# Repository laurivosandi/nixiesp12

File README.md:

# NixiESP12

## Intro

Yet another Nixie clock project!

Some highlights:

* K155ID1 driven IN-12A or IN-12B tubes for hour, minute, seconds. Use 36k resistors on these tubes.
* BS108 driven IN-6 or [similar 4*10mm neon bulbs](https://www.aliexpress.com/item/32344955038.html?spm=a2g0s.9042311.0.0.6ab14c4dCxpPZ0) for digit separation. Use 270k resistors on these bulbs.
* 74HC595 for serial to parallel conversion
* ESP8266 for time synchronization. Use 1k resistors for pull-up.
* LM1117-3.3V and LM1117-5V regulators for logic power supply
* No tube step up converter on-board, pin headers for connecting
  <a href="http://www.ebay.com/itm/DC-5V-12V-to-170V-DC-High-Voltage-NIXIE-Power-Supply-Module-PSU-NIXIE-TUBE-ERA-/322511957768?hash=item4b1735ef08">third party power supply</a>
* KiCad design with 3D models from http://miniwatt.info

Some KiCad screenshots:

## Install

Install dependencies on an Ubuntu 18.04 box:

```bash
apt install -y python3-pip wget picocom make
pip3 install adafruit-ampy esptool
```

Boot ESP8266 with program pin held low and flash MicroPython:

```bash
cd firmware
make erase
make flash
```

Reboot ESP8266, open serial to to the controller and format filesystem:

```
import os
os.umount('/')
os.VfsLfs2.mkfs(bdev)
os.mount(bdev, '/')
```

Finish with by uploading scripts:

```bash
make upload
```

Power cycle the device and via WiFi connect to the device,
network name is MicroPython-XXXXXX and password is micropythoN.
Navigate to http://192.168.4.1 to start the configuration wizard.

## Configuring

If firmware is unable to connect to preconfigured wireless network
or it is started up for the first time wireless network
with password `micropythoN` is created.

Connect to that wireless network and open http://192.168.4.1
in web browser to configure the clock.

## Assembly tips

Some cheap 1117V regulators don't offer short circuit protection
and once blown pass through input voltage,
make sure you get ones with protection otherwise you can fry ESP8266
or serial-to-parallel chips.

Once the PCB is milled or etched make sure you clean the 180V rails thoroughly,
that voltage is high enough to cross gaps of 0.1mm.
Once that happens it burns a thick dark trace into the fiberglass of PCB and
it's pretty tricky to clean up.
The PCB is designed with 0.4mm clearance to be compliant with HV designs.
This clearance of course assumes that PCB traces are covered.
Either use solder mask or conformal coating.

Use the bench power supply to gradually power up the device,
at 9V set current limiter to 0.5A max.
5V linear regulator can be omitted and bypassed if 5V wall adapter is always used.
Otherwise 6V-12V wall adapters are suitable,
Thincan DBE60 9V wall adapters are pretty much perfect for the job.
Note that the higher the input voltage the more power is dissipated
as heat on the 3.3V and 5V voltage regulators, thus at 12V the device gets really hot.

## Debugging

* If you get nonsense reading during boot up sequence 0..9 likely the connection between serial-to-parallel chips and high voltage drivers
  is flaky. Either there are shorted pins or there is no connection at all. Check soldering joints and check for shorts between lines and line to ground.
* If single tube doesn't light up likely the gas has escaped the tube, find replacement tube.
* If single digit does not light up likely the tube socket pin is mangled or it is not properly soldered on the side where the PCB trace runs.

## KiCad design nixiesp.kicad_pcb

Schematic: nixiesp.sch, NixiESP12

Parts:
C1, C3: C; C_Disc_D4.3mm_W1.9mm_P5.00mm
C2, C4: CP; CP_Radial_D8.0mm_P3.50mm
J1: Power 9-15V; TerminalBlock_Pheonix_PT-3.5mm_2pol
J2: ESP8266; Socket_Strip_Straight_2x04_Pitch2.54mm
J3, J10, J12: CONN_01X06; Pin_Header_Angled_1x06_Pitch2.54mm
J4, J6, J13: CONN_01X07; Pin_Header_Angled_1x07_Pitch2.54mm
J5, J27, J29: CONN_01X06; Socket_Strip_Straight_1x06_Pitch2.54mm
J9: CONN_01X05; Socket_Strip_Straight_1x05_Pitch2.54mm
J11, J14, J31: CONN_01X07; Socket_Strip_Straight_1x07_Pitch2.54mm
J15, J16, J17, J18, J19, J20, J21, J23, J24, J25: CONN_01X01; 1pin
N1: HX:MM:SS; russian-nixies-IN-12
N2: XH:MM:SS; russian-nixies-IN-12
N3: HH:MX:SS; russian-nixies-IN-12
N4: HH:XM:SS; russian-nixies-IN-12
N5: HH:MM:SX; russian-nixies-IN-12
N6: HH:MM:XS; russian-nixies-IN-12
N7, N8, N9, N10: IN-6; russian-nixies-IN-6
Q1, Q2, Q3, Q4: BS107; TO-92_Inline_Wide
R1, R2: 2.2k; R_Axial_DIN0207_L6.3mm_D2.5mm_P7.62mm_Horizontal
R7, R8, R9, R10: 15k; R_Axial_DIN0207_L6.3mm_D2.5mm_P7.62mm_Horizontal
R11, R12, R13, R14, R15, R16: 10k; R_Axial_DIN0207_L6.3mm_D2.5mm_P7.62mm_Horizontal
U1, U5, U8, U11, U13, U14: 74HC595; DIP-16_W7.62mm
U2, U3, U4, U6, U7, U9: K155ID1; DIP-16_W7.62mm
U10: LM1117-5.0; SOT-223
U12: LM1117-3.3; SOT-223

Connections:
/data: J2.3, R2.2, U8.14 (SER)
/latch: J2.5, R1.1, U1.12 (RCLK), U5.12 (RCLK), U8.12 (RCLK), U11.12 (RCLK), U13.12 (RCLK), U14.12 (RCLK)
unnamed: J1.2, J9.1, U10.3 (VI), U12.3 (VI)
unnamed: J3.2, U2.7
unnamed: J3.3, U2.6
unnamed: J3.5, U2.4
unnamed: J3.6, U2.3
unnamed: J4.2, U3.7
unnamed: J4.3, U3.6
unnamed: J4.5, U3.4
unnamed: J4.6, U3.3
unnamed: J4.7, Q1.2 (G)
unnamed: J5.1, U1.2 (QC)
unnamed: J5.2, U1.3 (QD)
unnamed: J5.3, U1.4 (QE)
unnamed: J5.5, U1.5 (QF)
unnamed: J5.6, U1.6 (QG)
unnamed: J6.2, U6.7
unnamed: J6.3, U6.6
unnamed: J6.5, U6.4
unnamed: J6.6, U6.3
unnamed: J6.7, Q3.2 (G)
unnamed: J10.1, Q2.2 (G)
unnamed: J10.2, U4.7
unnamed: J10.3, U4.6
unnamed: J10.5, U4.4
unnamed: J10.6, U4.3
unnamed: J11.2, U11.3 (QD)
unnamed: J11.3, U11.4 (QE)
unnamed: J11.5, U11.5 (QF)
unnamed: J11.6, U11.6 (QG)
unnamed: J11.7, U1.1 (QB)
unnamed: J12.1, Q4.2 (G)
unnamed: J12.2, U7.7
unnamed: J12.3, U7.6
unnamed: J12.5, U7.4
unnamed: J12.6, U7.3
unnamed: J13.2, U9.7
unnamed: J13.3, U9.6
unnamed: J13.5, U9.4
unnamed: J13.6, U9.3
unnamed: J13.7, R7.1, R8.1, R9.1, R10.1, R11.1, R12.1, R13.1, R14.1, R15.1, R16.1
unnamed: J14.2, U13.3 (QD)
unnamed: J14.3, U13.4 (QE)
unnamed: J14.5, U13.5 (QF)
unnamed: J14.6, U13.6 (QG)
unnamed: J14.7, U5.1 (QB)
unnamed: J27.2, U8.3 (QD)
unnamed: J27.3, U8.4 (QE)
unnamed: J27.5, U8.5 (QF)
unnamed: J27.6, U8.6 (QG)
unnamed: J29.1, U5.2 (QC)
unnamed: J29.2, U5.3 (QD)
unnamed: J29.3, U5.4 (QE)
unnamed: J29.5, U5.5 (QF)
unnamed: J29.6, U5.6 (QG)
unnamed: J31.2, U14.3 (QD)
unnamed: J31.3, U14.4 (QE)
unnamed: J31.5, U14.5 (QF)
unnamed: J31.6, U14.6 (QG)
unnamed: J9.5, J31.7
unnamed: N1.0, U7.10
unnamed: N1.1, U7.14
unnamed: N1.2, U7.2
unnamed: N1.3, U7.15
unnamed: N1.4, U7.16
unnamed: N1.5, U7.1
unnamed: N1.6, U7.13
unnamed: N1.7, U7.11
unnamed: N1.8, U7.8
unnamed: N1.9, U7.9
unnamed: N1.A, R15.2
unnamed: N2.0, U9.10
unnamed: N2.1, U9.14
unnamed: N2.2, U9.2
unnamed: N2.3, U9.15
unnamed: N2.4, U9.16
unnamed: N2.5, U9.1
unnamed: N2.6, U9.13
unnamed: N2.7, U9.11
unnamed: N2.8, U9.8
unnamed: N2.9, U9.9
unnamed: N2.A, R16.2
unnamed: N3.0, U4.10
unnamed: N3.1, U4.14
unnamed: N3.2, U4.2
unnamed: N3.3, U4.15
unnamed: N3.4, U4.16
unnamed: N3.5, U4.1
unnamed: N3.6, U4.13
unnamed: N3.7, U4.11
unnamed: N3.8, U4.8
unnamed: N3.9, U4.9
unnamed: N3.A, R13.2
unnamed: N4.0, U6.10
unnamed: N4.1, U6.14
unnamed: N4.2, U6.2
unnamed: N4.3, U6.15
unnamed: N4.4, U6.16
unnamed: N4.5, U6.1
unnamed: N4.6, U6.13
unnamed: N4.7, U6.11
unnamed: N4.8, U6.8
unnamed: N4.9, U6.9
unnamed: N4.A, R14.2
unnamed: N5.0, U2.10
unnamed: N5.1, U2.14
unnamed: N5.2, U2.2
unnamed: N5.3, U2.15
unnamed: N5.4, U2.16
unnamed: N5.5, U2.1
unnamed: N5.6, U2.13
unnamed: N5.7, U2.11
unnamed: N5.8, U2.8
unnamed: N5.9, U2.9
unnamed: N5.A, R11.2
unnamed: N6.0, U3.10
unnamed: N6.1, U3.14
unnamed: N6.2, U3.2
unnamed: N6.3, U3.15
unnamed: N6.4, U3.16
unnamed: N6.5, U3.1
unnamed: N6.6, U3.13
unnamed: N6.7, U3.11
unnamed: N6.8, U3.8
unnamed: N6.9, U3.9
unnamed: N6.A, R12.2
unnamed: N7.A, R10.2
unnamed: N7.K, Q4.1 (D)
unnamed: N8.A, R7.2
unnamed: N8.K, Q1.1 (D)
unnamed: N9.A, R8.2
unnamed: N9.K, Q2.1 (D)
unnamed: N10.A, R9.2
unnamed: N10.K, Q3.1 (D)
unnamed: U1.9 (~QH), U14.14 (SER)
unnamed: U1.14 (SER), U11.9 (~QH)
unnamed: U5.9 (~QH), U11.14 (SER)
unnamed: U5.14 (SER), U13.9 (~QH)
unnamed: U8.9 (~QH), U13.14 (SER)

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
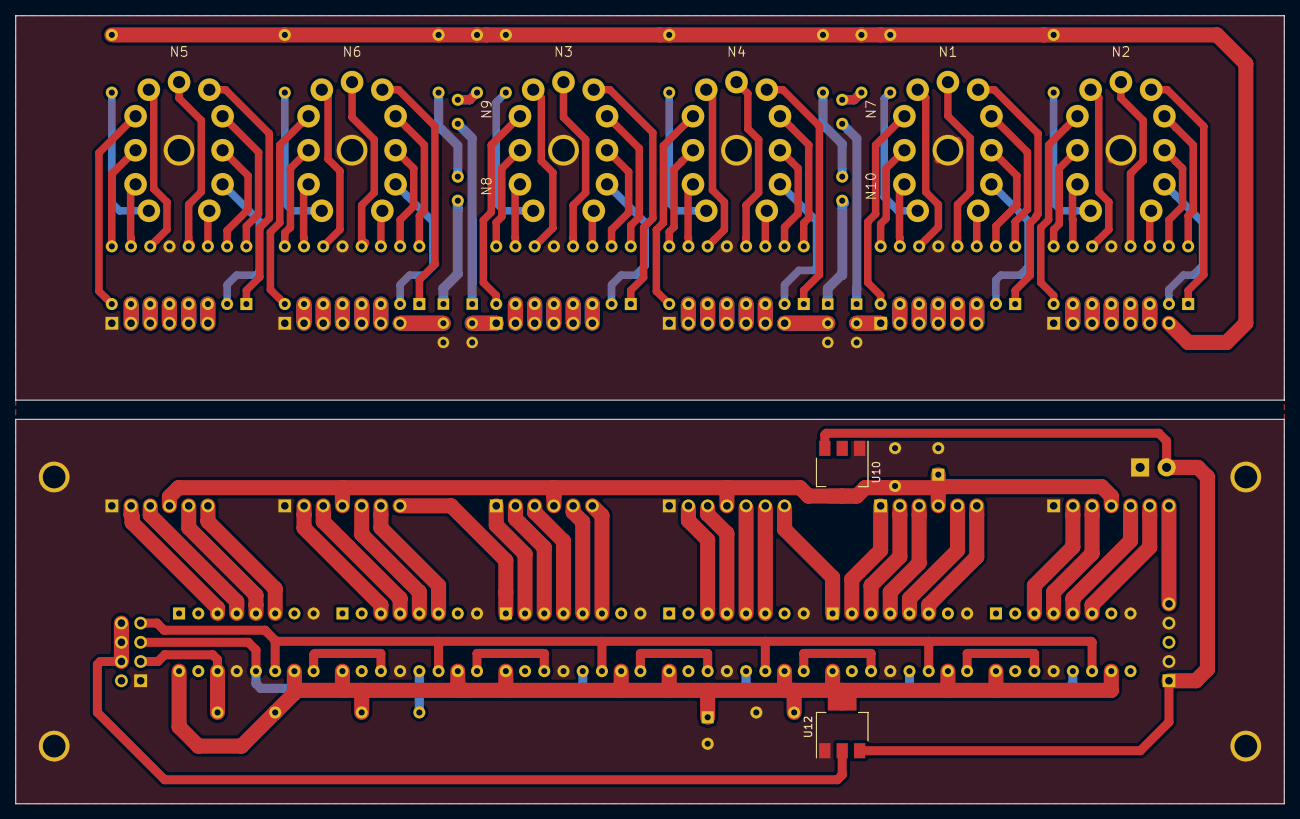
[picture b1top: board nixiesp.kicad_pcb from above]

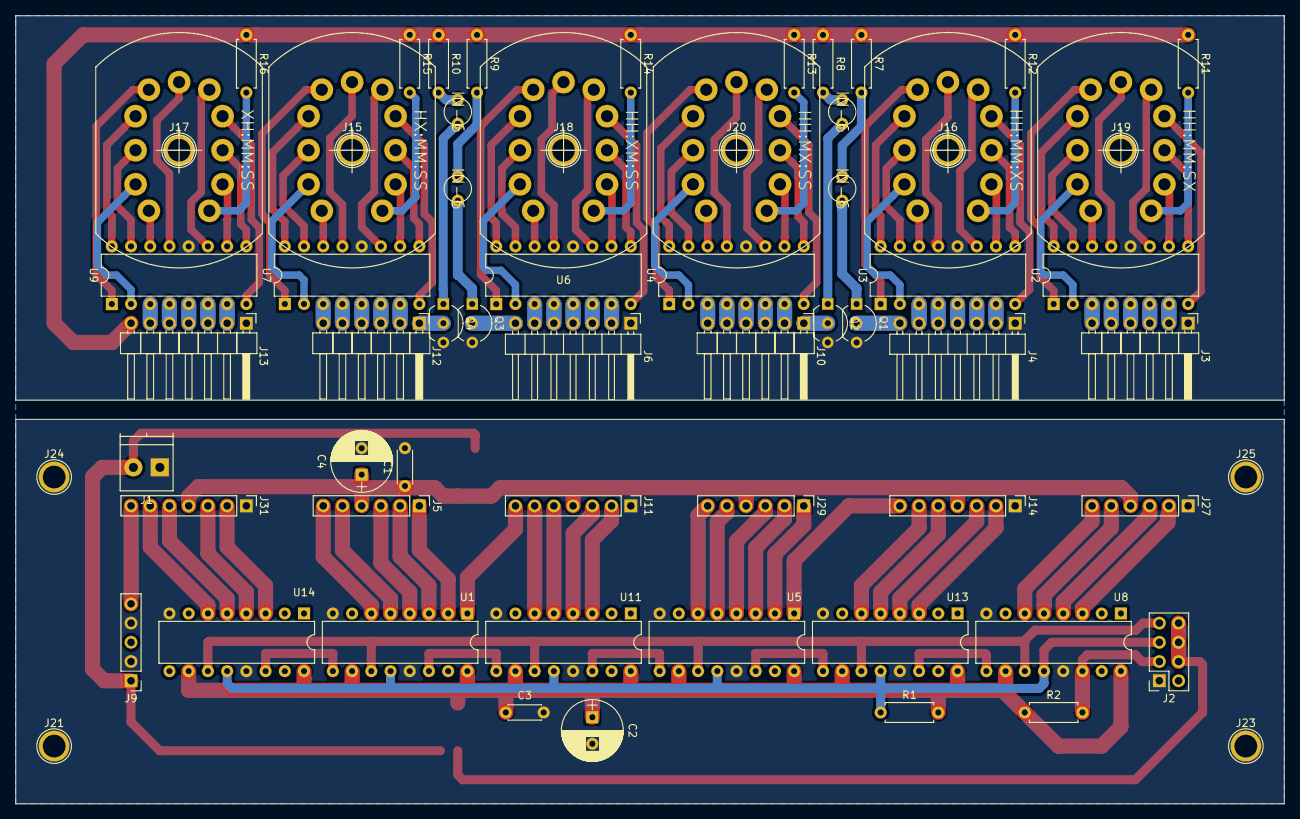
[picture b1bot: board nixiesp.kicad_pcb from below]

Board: 2 copper layers, 167.6 x 104.1 mm, 69 parts (67 on the bottom side), 143 nets.

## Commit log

2017-06-11 Rotate tubes and other fixes
2017-07-13 Add MicroPython snippets
2017-07-14 Instructions for flashing ESP8266
2017-08-08 Add photo
2017-08-08 Hopefully final changes
2017-08-08 More assembly tips
2017-08-25 Add periodic NTP resync
2018-11-25 Perfected design
2018-12-19 Fixed clock drift and added setup wizard
2018-12-23 Final fixes
2018-12-23 Fix main.py
2018-12-23 Add firmware makefile
2018-12-23 Fix README.md, remove nixiesp.bin
2018-12-23 More README fixes
2021-07-07 Add DST and boot up sequence
2021-07-11 Increase pin socket diameter to 1.6mm
2021-07-11 Update firmware Makefile
2021-07-21 Bump Micropython version
2021-07-27 More specific information about components
2024-07-21 Plastic parts additions and fixes
2024-10-03 Bump PCB thickness
2024-10-03 Add Arduino rewrite of firmware
2025-07-29 More AI slop
2025-09-10 Clean up metrics
2025-09-10 Report boot time only once it has meaningful value
2025-10-14 Add Prometheus monitoring
2025-12-14 Fix zero hour handling for 12-hour mode
2025-12-14 Add Woodpecker CI
2026-02-05 Build images for main branch
2026-06-17 GitHub pipeline improvements
2026-06-17 Bump setup-arduino-cli action version
